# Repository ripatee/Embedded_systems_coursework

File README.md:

# Embedded_systems_coursework
Course work for Embedded systems project -course. Project is nRF9160 based temperature sensor with an eINK display.

## Features
- Based on nRF9160 SIP
- Measures (at least) temperature and humidity
- Shows measurements at eINK screen
- Sends measurements over M-LTE or NB-IOT
- Additionally sends current GPS coordinates
- Battery powered

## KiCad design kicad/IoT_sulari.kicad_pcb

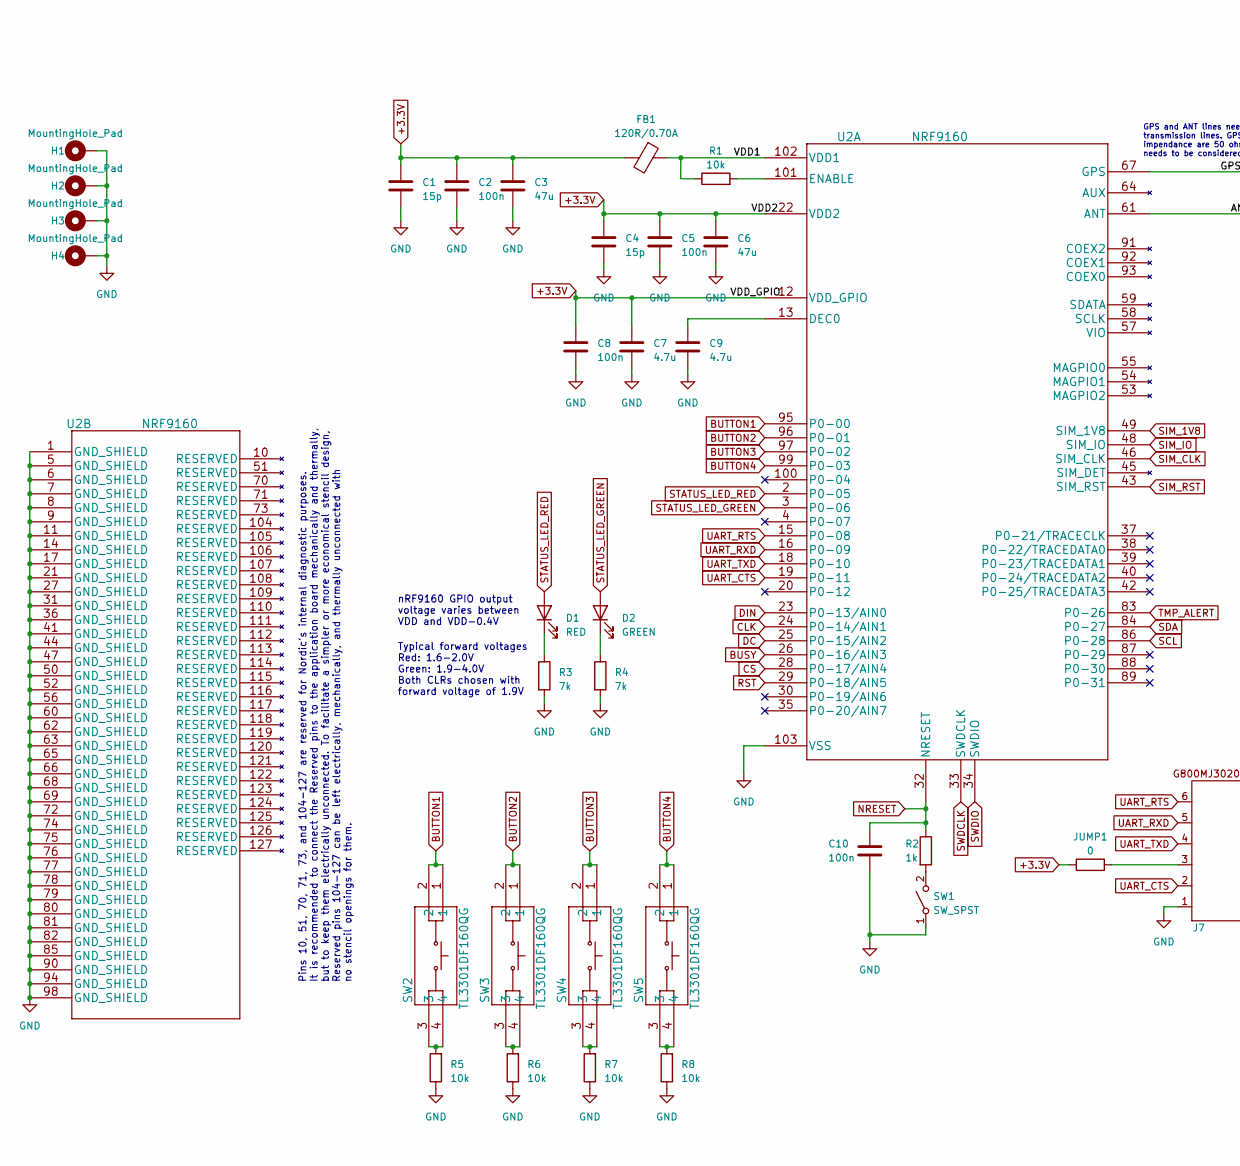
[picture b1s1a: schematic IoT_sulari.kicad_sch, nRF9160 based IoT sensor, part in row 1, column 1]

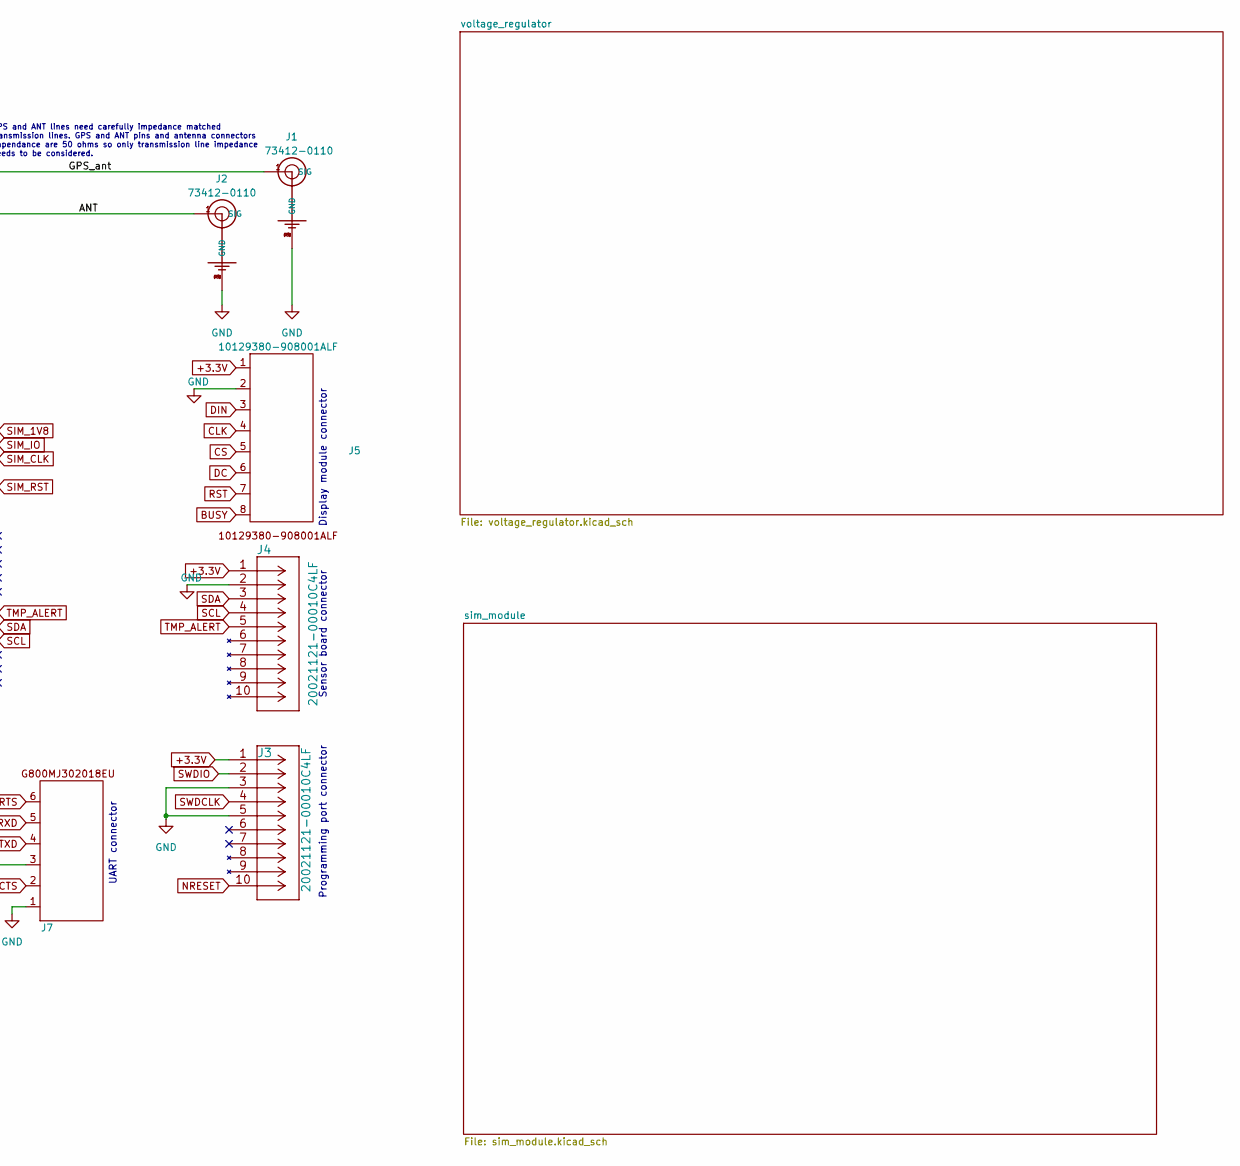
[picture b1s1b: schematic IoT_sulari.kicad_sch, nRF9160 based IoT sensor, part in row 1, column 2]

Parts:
C1, C4: 15p; C_0603_1608Metric_Pad1.08x0.95mm_HandSolder; Digikey 1292-1487-1-ND
C2, C5, C8, C10: 100n; C_0603_1608Metric_Pad1.08x0.95mm_HandSolder; Digikey 587-1245-1-ND
C3, C6: 47u; C_0603_1608Metric_Pad1.08x0.95mm_HandSolder; Digikey 490-GRM188R60G476ME01DCT-ND
C7, C9: 4.7u; C_0603_1608Metric_Pad1.08x0.95mm_HandSolder; Digikey 1276-1045-1-ND
D1: RED; LED_0603_1608Metric_Pad1.05x0.95mm_HandSolder; Digikey 1080-1400-1-ND
D2: GREEN; LED_0603_1608Metric_Pad1.05x0.95mm_HandSolder; Digikey 492-2523-1-ND
FB1: 120R/0.70A; R_0402_1005Metric_Pad0.72x0.64mm_HandSolder; Digikey 445-MMZ1005S121HTD25CT-ND
H1, H2, H3, H4: MountingHole_Pad; MountingHole_3.2mm_M3_Pad_Via
J1, J2: 73412-0110; MOLEX_73412-0110; Digikey WM5587CT-ND
J3, J4: 20021121-00010C4LF; Digikey 609-3695-1-ND
J5: 10129380-908001ALF; Digikey 10129380-908001ALF-ND
J7: G800MJ302018EU; Digikey 664-G800MJ302018EUCT-ND
JUMP1: 0; R_0805_2012Metric_Pad1.20x1.40mm_HandSolder
R1, R5, R6, R7, R8: 10k; R_0603_1608Metric_Pad0.98x0.95mm_HandSolder; Digikey RNCP0603FTD10K0CT-ND
R2: 1k; R_0603_1608Metric_Pad0.98x0.95mm_HandSolder; Digikey RNCP0603FTD1K00CT-ND
R3, R4: 7k; R_0603_1608Metric_Pad0.98x0.95mm_HandSolder; Digikey 311-6.98KHRCT-ND
SW1: SW_SPST; TL3302BF180QG; Digikey EG2529CT-ND
SW2, SW3, SW4, SW5: TL3301DF160QG
U2: NRF9160; NRF9160-SICA-B1A-R; Digikey 4823-NRF9160-SICA-B1A-RCT-ND

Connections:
+3.3V: C1.1, C2.1, C3.1, C4.1, C5.1, C6.1, C7.1, C8.1, FB1.2, J3.1, J4.1, J5.1, JUMP1.1, U2.12 (VDD_GPIO), U2.22 (VDD2); also elsewhere on the board
/ANT: J2.1 (SIG), U2.61 (ANT)
/GPS_ant: J1.1 (SIG), U2.67 (GPS)
/VDD1: FB1.1, R1.1, U2.102 (VDD1)
BUSY: J5.8, U2.26 (P0-16/AIN3)
BUTTON1: SW2.1, SW2.2, U2.95 (P0-00)
BUTTON2: SW3.1, SW3.2, U2.96 (P0-01)
BUTTON3: SW4.1, SW4.2, U2.97 (P0-02)
BUTTON4: SW5.1, SW5.2, U2.99 (P0-03)
CLK: J5.4, U2.24 (P0-14/AIN1)
CS: J5.5, U2.28 (P0-17/AIN4)
DC: J5.6, U2.25 (P0-15/AIN2)
DIN: J5.3, U2.23 (P0-13/AIN0)
GND: C1.2, C2.2, C3.2, C4.2, C5.2, C6.2, C7.2, C8.2, C9.2, C10.2, H1.1, H2.1, H3.1, H4.1, J1.2 (GND), J1.3 (GND), J1.4 (GND), J2.2 (GND), J2.3 (GND), J2.4 (GND), J3.3, J3.5, J4.2, J5.2, J7.1, R3.2, R4.2, R5.1, R6.1, R7.1, R8.1, SW1.1 (A), U2.1 (GND_SHIELD), U2.5 (GND_SHIELD), U2.6 (GND_SHIELD), U2.7 (GND_SHIELD), U2.8 (GND_SHIELD), U2.9 (GND_SHIELD), U2.11 (GND_SHIELD), U2.14 (GND_SHIELD), U2.17 (GND_SHIELD), U2.21 (GND_SHIELD), U2.27 (GND_SHIELD), U2.31 (GND_SHIELD), U2.36 (GND_SHIELD), U2.41 (GND_SHIELD), U2.44 (GND_SHIELD), U2.47 (GND_SHIELD), U2.50 (GND_SHIELD), U2.52 (GND_SHIELD), U2.56 (GND_SHIELD), U2.60 (GND_SHIELD), U2.62 (GND_SHIELD), U2.63 (GND_SHIELD), U2.65 (GND_SHIELD), U2.66 (GND_SHIELD), U2.68 (GND_SHIELD), U2.69 (GND_SHIELD), U2.72 (GND_SHIELD), U2.74 (GND_SHIELD), U2.75 (GND_SHIELD), U2.76 (GND_SHIELD), U2.77 (GND_SHIELD), U2.78 (GND_SHIELD), U2.79 (GND_SHIELD), U2.80 (GND_SHIELD), U2.81 (GND_SHIELD), U2.82 (GND_SHIELD), U2.85 (GND_SHIELD), U2.90 (GND_SHIELD), U2.94 (GND_SHIELD), U2.98 (GND_SHIELD), U2.103 (VSS); also elsewhere on the board
NRESET: C10.1, J3.10, R2.1, U2.32 (NRESET)
unnamed: D1.1 (K), R3.1
unnamed: D2.1 (K), R4.1
unnamed 17: J7.3, JUMP1.2; also elsewhere on the board
unnamed: R5.2, SW2.3, SW2.4
unnamed: R6.2, SW3.3, SW3.4
unnamed: R7.2, SW4.3, SW4.4
unnamed: R8.2, SW5.3, SW5.4
unnamed: R2.2, SW1.2 (B)
unnamed: C9.1, U2.13 (DEC0)
unnamed: R1.2, U2.101 (ENABLE)
RST: J5.7, U2.29 (P0-18/AIN5)
SCL: J4.4, U2.86 (P0-28)
SDA: J4.3, U2.84 (P0-27)
SIM_1V8: U2.49 (SIM_1V8); also elsewhere on the board
SIM_CLK: U2.46 (SIM_CLK); also elsewhere on the board
SIM_IO: U2.48 (SIM_IO); also elsewhere on the board
SIM_RST: U2.43 (SIM_RST); also elsewhere on the board
STATUS_LED_GREEN: D2.2 (A), U2.3 (P0-06)
STATUS_LED_RED: D1.2 (A), U2.2 (P0-05)
SWDCLK: J3.4, U2.33 (SWDCLK)
SWDIO: J3.2, U2.34 (SWDIO)
TMP_ALERT: J4.5, U2.83 (P0-26)
UART_CTS: J7.2, U2.19 (P0-11)
UART_RTS: J7.6, U2.15 (P0-08)
UART_RXD: J7.5, U2.16 (P0-09)
UART_TXD: J7.4, U2.18 (P0-10)

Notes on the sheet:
Sensor board connector
Display module connector
Programming port connector
Pins 10, 51, 70, 71, 73, and 104-127 are reserved for Nordic's internal diagnostic purposes. It is recommended to connect the Reserved pins to the application board mechanically and thermally, but to keep them electrically unconnected. To facilitate a simpler or more economical stencil design, Rese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
nRF9160 GPIO output voltage varies between VDD and VDD-0.4V
UART connector
GPS and ANT lines need carefully impedance matched transmission lines. GPS and ANT pins and antenna connectors impendance are 50 ohms so only transmission line impedance needs to be considered.
Typical forward voltages Red: 1.6-2.0V Green: 1.9-4.0V Both CLRs chosen with forward voltage of 1.9V

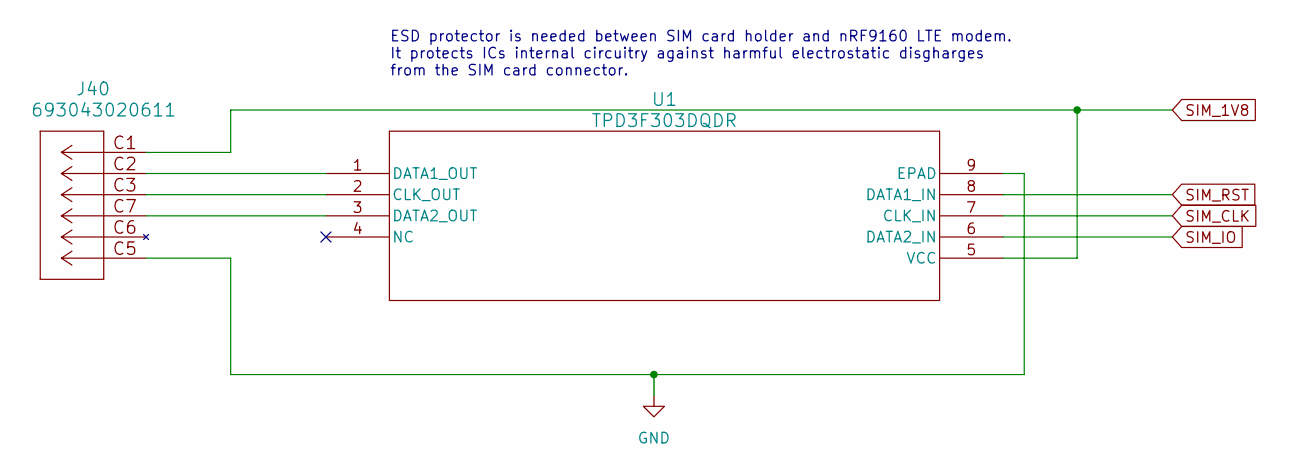
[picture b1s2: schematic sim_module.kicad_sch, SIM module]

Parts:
J40: 693043020611; Digikey 296-28299-1-ND
U1: TPD3F303DQDR

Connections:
GND: J40.C5, U1.9 (EPAD); also elsewhere on the board
unnamed 27: J40.C3, U1.2 (CLK_OUT); also elsewhere on the board
unnamed 28: J40.C2, U1.1 (DATA1_OUT); also elsewhere on the board
unnamed 29: J40.C7, U1.3 (DATA2_OUT); also elsewhere on the board
SIM_1V8: J40.C1, U1.5 (VCC); also elsewhere on the board

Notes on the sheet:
ESD protector is needed between SIM card holder and nRF9160 LTE modem. It protects ICs internal circuitry against harmful electrostatic disgharges from the SIM card connector.

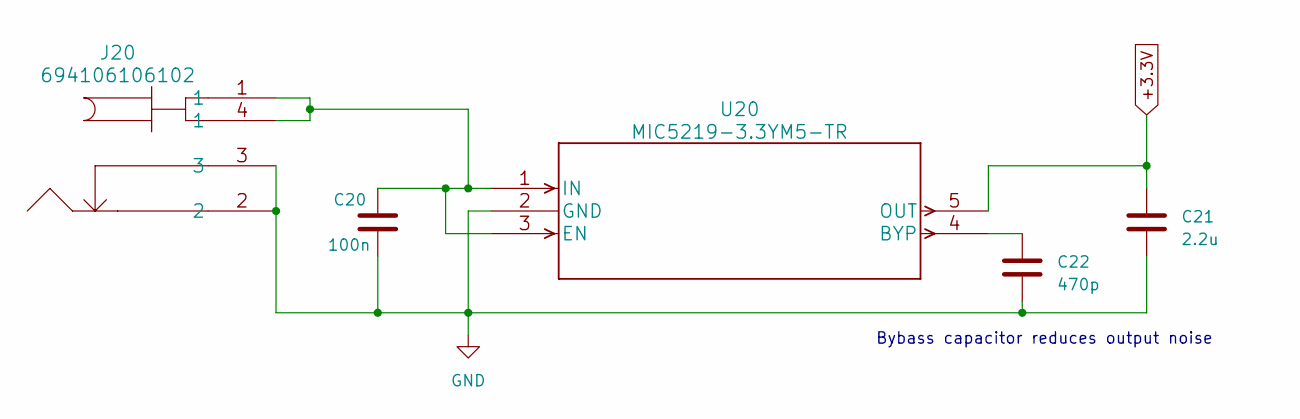
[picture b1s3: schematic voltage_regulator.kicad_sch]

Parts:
C20: 100n; C_0603_1608Metric_Pad1.08x0.95mm_HandSolder; Digikey 587-1245-1-ND
C21: 2.2u; C_0603_1608Metric_Pad1.08x0.95mm_HandSolder; Digikey 587-1430-1-ND
C22: 470p; C_0603_1608Metric_Pad1.08x0.95mm_HandSolder; Digikey 1292-1530-1-ND
J20: 694106106102; Digikey 732-5929-1-ND
U20: MIC5219-3.3YM5-TR; Digikey 576-1281-1-ND

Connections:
+3.3V: C21.1, U20.5 (OUT); also elsewhere on the board
GND: C20.2, C21.2, C22.2, J20.2, J20.3, U20.2 (GND); also elsewhere on the board
unnamed: C22.1, U20.4 (BYP)
unnamed: C20.1, J20.1, J20.4 (1), U20.1 (IN), U20.3 (EN)

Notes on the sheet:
Bybass capacitor reduces output noise

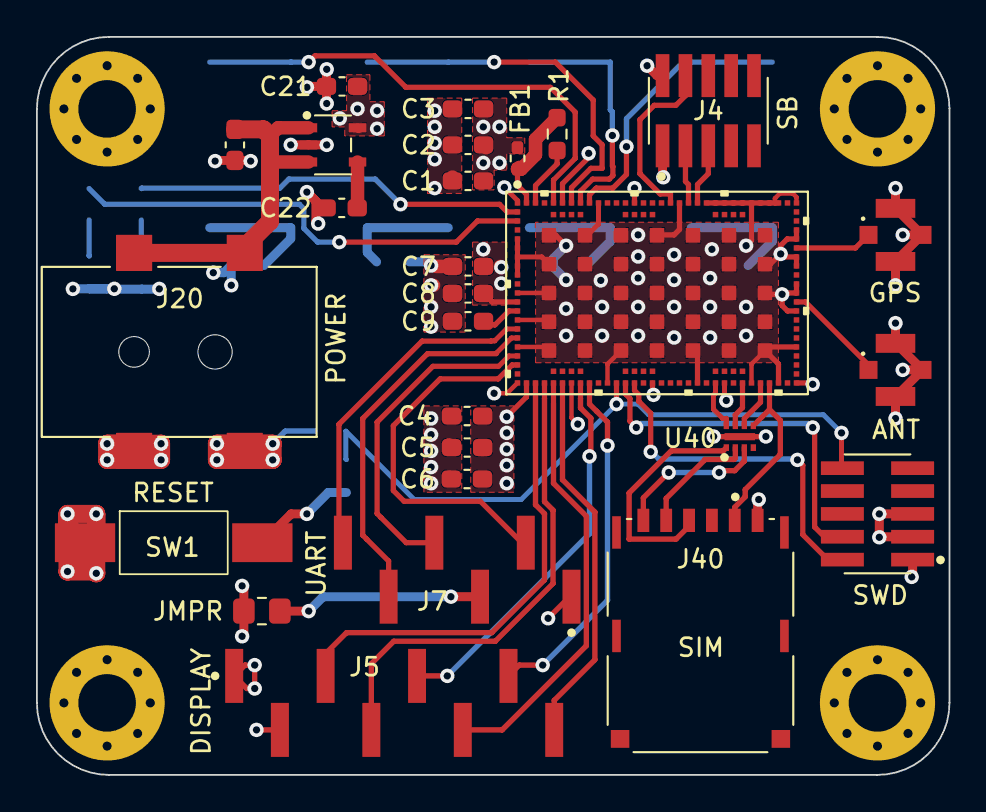
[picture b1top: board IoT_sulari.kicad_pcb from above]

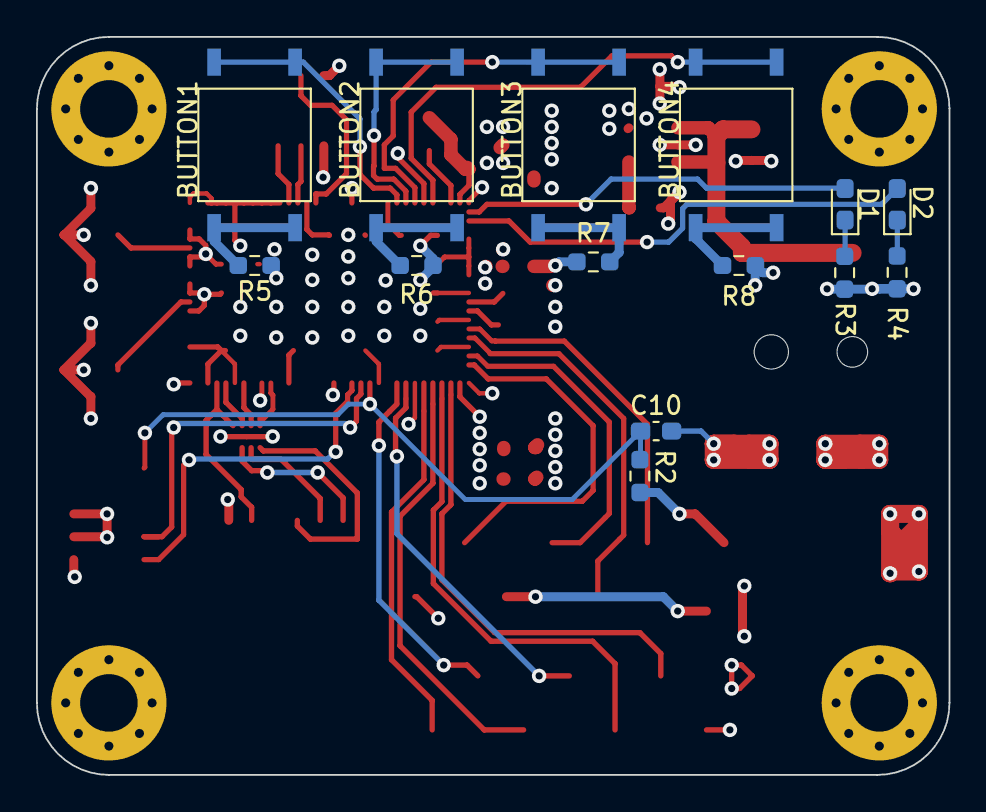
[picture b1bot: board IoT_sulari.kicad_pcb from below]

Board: 4 copper layers, 50.7 x 41.0 mm, 45 parts (14 on the bottom side), 46 nets.

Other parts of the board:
JMPR: 0; R_0805_2012Metric_Pad1.20x1.40mm_HandSolder
U40: TPD3F303DPVR

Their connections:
+3.3V: JMPR.1; also elsewhere on the board
GND: U40.9 (EPAD); also elsewhere on the board
unnamed 17: JMPR.2; also elsewhere on the board
unnamed 27: U40.2 (CLK_OUT); also elsewhere on the board
unnamed 28: U40.1 (DATA1_OUT); also elsewhere on the board
unnamed 29: U40.3 (DATA2_OUT); also elsewhere on the board
SIM_1V8: U40.5 (VCC); also elsewhere on the board
SIM_CLK: U40.7 (CLK_IN); also elsewhere on the board
SIM_IO: U40.6 (DATA2_IN); also elsewhere on the board
SIM_RST: U40.8 (DATA1_IN); also elsewhere on the board

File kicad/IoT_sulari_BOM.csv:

"Reference","Value","Footprint","Datasheet","Digikey","MANUFACTURER","Qty"
"C1, C4","15p","Capacitor_SMD:C_0603_1608Metric_Pad1.08x0.95mm_HandSolder","~","1292-1487-1-ND","","2"
"C2, C5, C7, C10, C20","100n","Capacitor_SMD:C_0603_1608Metric_Pad1.08x0.95mm_HandSolder","~","587-1245-1-ND","","5"
"C3, C6","47u","Capacitor_SMD:C_0603_1608Metric_Pad1.08x0.95mm_HandSolder","~","490-GRM188R60G476ME01DCT-ND","","2"
"C8, C9","4.7u","Capacitor_SMD:C_0603_1608Metric_Pad1.08x0.95mm_HandSolder","~","1276-1045-1-ND","","2"
"C21","2.2u","Capacitor_SMD:C_0603_1608Metric_Pad1.08x0.95mm_HandSolder","~","587-1430-1-ND","","1"
"C22","470p","Capacitor_SMD:C_0603_1608Metric_Pad1.08x0.95mm_HandSolder","~","1292-1530-1-ND","","1"
"D1","RED","LED_SMD:LED_0603_1608Metric_Pad1.05x0.95mm_HandSolder","~","1080-1400-1-ND","","1"
"D2","GREEN","LED_SMD:LED_0603_1608Metric_Pad1.05x0.95mm_HandSolder","~","492-2523-1-ND","","1"
"FB1","120R/0.70A","Resistor_SMD:R_0402_1005Metric_Pad0.72x0.64mm_HandSolder","~","445-MMZ1005S121HTD25CT-ND","","1"
"H1-H4","MountingHole_Pad","MountingHole:MountingHole_3.2mm_M3_Pad_Via","~","","","4"
"J1, J2","73412-0110","73412-0110:MOLEX_73412-0110","","WM5587CT-ND","Molex","2"
"J3, J4, J6","20021121-00010C4LF","20021121-00010C4LF:20021121-00010C4LF","","609-3695-1-ND","","3"
"J7","","G800MJ302018EU:G800MJ302018EU","","664-G800MJ302018EUCT-ND","","1"
"J20","694106106102","694106106102:694106106102","","732-5929-1-ND","","1"
"J40","693043020611","693043020611:693043020611","","296-28299-1-ND","","1"
"R1, R5-R8","10k","Resistor_SMD:R_0603_1608Metric_Pad0.98x0.95mm_HandSolder","~","RNCP0603FTD10K0CT-ND","","5"
"R2","1k","Resistor_SMD:R_0603_1608Metric_Pad0.98x0.95mm_HandSolder","~","RNCP0603FTD1K00CT-ND","","1"
"R3, R4","7k","Resistor_SMD:R_0603_1608Metric_Pad0.98x0.95mm_HandSolder","~","311-6.98KHRCT-ND","","2"
"SW1","SW_SPST","TL3302BF180QG:TL3302BF180QG","","EG2529CT-ND","","1"
"SW2-SW5","TL3301DF160QG","TL3301DF160QG:TL3301DF160QG","","","","4"
"U2","NRF9160","NRF-9160-SICA-B1A-R:NRF9160-SICA-B1A-R","","4823-NRF9160-SICA-B1A-RCT-ND","","1"
"U20","MIC5219-3.3YM5-TR","MIC5219-3.3YM5-TR:MIC5219-3.3YM5-TR","","576-1281-1-ND","","1"
"U40","TPD3F303DPVR","TPD3F303DPVR:TPD3F303DPVR","","732-5954-1-ND","","1"

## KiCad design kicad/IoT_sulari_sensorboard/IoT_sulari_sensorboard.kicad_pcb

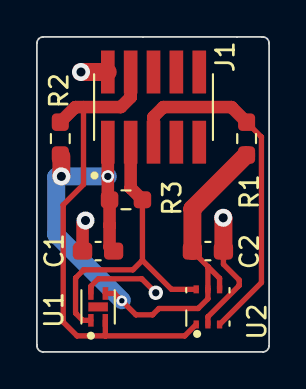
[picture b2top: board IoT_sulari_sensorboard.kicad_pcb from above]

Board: 2 copper layers, 12.9 x 17.5 mm, 8 parts (0 on the bottom side), 5 nets.

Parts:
C1, C2: 100n; C_0603_1608Metric_Pad1.08x0.95mm_HandSolder
J1: 20021121-00010C4LF
R1, R2, R3: 5k; R_0603_1608Metric_Pad0.98x0.95mm_HandSolder
U1: SHT40-AD1B-R3; SHT40-AD1B-R2
U2: TMP117MAIDRVT

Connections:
/GND: C1.2, C2.2, J1.2, U1.4 (VSS), U2.2 (GND)
/SCL: J1.4, R2.2, U1.2 (SCL), U2.1 (SCL)
/SDA: J1.3, R3.2, U1.1 (SDA), U2.6 (SDA)
/TMP_ALERT: J1.5, R1.2, U2.3 (ALERT)
/VCC: C1.1, C2.1, J1.1, R1.1, R2.1, R3.1, U1.3 (VDD), U2.4 (ADD0), U2.5 (V+)

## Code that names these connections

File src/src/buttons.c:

#include <zephyr/device.h>
#include <zephyr/devicetree.h>
#include <zephyr/drivers/gpio.h>
#include <zephyr/logging/log.h>

#include "buttons.h"
#include "sms_wrapper.h"
#include "sensors.h"

#define SW0_NODE    DT_ALIAS(sw0)
#define SW1_NODE    DT_ALIAS(sw1)
#define SW2_NODE    DT_ALIAS(sw2)
#define SW3_NODE    DT_ALIAS(sw3)

LOG_MODULE_REGISTER(BUTTONS, LOG_LEVEL_DBG);

static const struct gpio_dt_spec button0 = GPIO_DT_SPEC_GET(SW0_NODE, gpios);
static const struct gpio_dt_spec button1 = GPIO_DT_SPEC_GET(SW1_NODE, gpios);
static const struct gpio_dt_spec button2 = GPIO_DT_SPEC_GET(SW2_NODE, gpios);
static const struct gpio_dt_spec button3 = GPIO_DT_SPEC_GET(SW3_NODE, gpios);

static struct gpio_callback button0_cb_data;
static struct gpio_callback button1_cb_data;
static struct gpio_callback button2_cb_data;
static struct gpio_callback button3_cb_data;

static void button0_cb(const struct device *dev, struct gpio_callback *cb, uint32_t pins)
{
    LOG_INF("Button 0 pressed.");
}

static void button1_cb(const struct device *dev, struct gpio_callback *cb, uint32_t pins)
{
    LOG_INF("Button 1 pressed.");
}

static void button2_cb(const struct device *dev, struct gpio_callback *cb, uint32_t pins)
{
    LOG_INF("Button 2 pressed.");
}

static void button3_cb(const struct device *dev, struct gpio_callback *cb, uint32_t pins)
{
    LOG_INF("Button 3 pressed.");
}

void buttons_init(void)
{
    int ret;

    if (!device_is_ready(button0.port)) {
        return;
    }

    if (!device_is_ready(button1.port)) {
        return;
    }

    if (!device_is_ready(button2.port)) {
        return;
    }

    if (!device_is_ready(button3.port)) {
        return;
    }

    ret = gpio_pin_configure_dt(&button0, GPIO_INPUT);
	if (ret < 0) {
		return;
	}

    ret = gpio_pin_configure_dt(&button1, GPIO_INPUT);
	if (ret < 0) {
		return;
	}

    ret = gpio_pin_configure_dt(&button2, GPIO_INPUT);
	if (ret < 0) {
		return;
	}

    ret = gpio_pin_configure_dt(&button3, GPIO_INPUT);
	if (ret < 0) {
		return;
	}

    ret = gpio_pin_interrupt_configure_dt(&button0, GPIO_INT_EDGE_TO_ACTIVE );
    ret = gpio_pin_interrupt_configure_dt(&button1, GPIO_INT_EDGE_TO_ACTIVE );
    ret = gpio_pin_interrupt_configure_dt(&button2, GPIO_INT_EDGE_TO_ACTIVE );
    ret = gpio_pin_interrupt_configure_dt(&button3, GPIO_INT_EDGE_TO_ACTIVE );

    gpio_init_callback(&button0_cb_data, button0_cb, BIT(button0.pin)); 	
    gpio_init_callback(&button1_cb_data, button1_cb, BIT(button1.pin)); 	
    gpio_init_callback(&button2_cb_data, button2_cb, BIT(button2.pin)); 	
    gpio_init_callback(&button3_cb_data, button3_cb, BIT(button3.pin)); 	

    gpio_add_callback(button0.port, &button0_cb_data);
    gpio_add_callback(button1.port, &button1_cb_data);
    gpio_add_callback(button2.port, &button2_cb_data);
    gpio_add_callback(button3.port, &button3_cb_data);
}

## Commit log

2023-01-25 Add placeholder files
2023-03-02 Initialize KiCad project
2023-03-02 Testing kicad
2023-03-02 Add .gitignore, remove backups folder
2023-03-02 Add project specifiaciton in LaTeX format
2023-03-02 Added test file
2023-03-02 deleted test file
2023-03-08 testi
2023-03-14 Add nRF9160 to KiCad project
2023-03-16 added TCR2EF33 symbol to kicad
2023-03-16 Added NRF9160 symbol and footprint
2023-03-16 Added TMP117, HDC2010, TPD3F3 and TCR2EF33 symbols to KiCad and component documents to doc.
2023-03-17 Added hierarchical sheets to different components
2023-03-21 Updated nrf9160 symbols for easier use, added sim card holder and doc, added first connections to mcu
2023-03-22 Kosteussensori ja regulaattori footprintit
2023-03-22 added power jack and usb connector
2023-03-23 Updated USB module
2023-03-24 sensorboard modification, regulator modification, datasheets
2023-03-24 ESD component fo USB
2023-03-24 voltage regulator update
2023-03-24 added status leds
2023-03-24 sensorboard schema + esd datasheet
2023-03-24 added comments and muokkasin komponenttiennumeroinnin selvemmäksi.
2023-03-24 nreset
2023-03-24 added antenna connector
2023-03-28 Added Digikey part number and footprint to symbols, added signal TMP_ALERT
2023-03-28 Added buttons and connectors
2023-03-30 6-pin connector footprint and symbol
2023-03-30 schematic editing, led selection
2023-03-30 footprint 9-pin
2023-03-30 kommitti
2023-04-06 USB-module delete
2023-04-06 added footprints and Digikey codes
2023-04-06 reset button footprint
2023-04-06 PCB update
2023-04-06 Reset button footprint added to pcb
2023-04-11 Updated PCB design rules and layout to correct placing around nRF9160
2023-04-12 viesti
2023-04-12 updated PCB
2023-04-14 kytkimen siirto
2023-04-14 TL3302 footprint edit
2023-04-14 moro
2023-04-14 sensorboard project add
2023-04-14 added board outline and inner copper layers, layout finalization
2023-04-14 sensorboard pcb drawing
2023-04-14 routing
2023-04-19 Finished routing and added vias
2023-04-21 csv document
2023-04-21 csv delete
2023-04-25 sensorboard edit
2023-05-05 Fixed drc errors for PCB
2023-05-05 sensorboard modify and mainboard connector add
2023-05-05 sensorboard DRC fix
2023-05-05 changed Display connector
2023-05-05 Edited copper fill zones, final touches
2023-05-05 ESD change
2023-05-09 Add sensorboard manufacturing files
2023-05-09 Revert "ESD change"
    This reverts commit acabe66db7bce87ed7ccd6d28b87d0a8866a87e9.
2023-05-09 Regenerate main board manufacturing files
2023-09-23 Initial commit for bring-up
2023-09-29 Test codes to test different peripherals
2023-09-30 Add minimal sensor functionality (logs values to console)
2023-09-30 Add buttons skeleton
2023-09-30 Add LTE skeleton
2023-10-02 PoC MQTT functionality
2023-10-02 Correct indentation
2023-10-02 Add SMS functionality
2023-10-02 Change CONFIG_SMS_RECEIVER_NUMBER to empty string
2023-10-02 Remove not needed header includes
2023-10-08 Start EPD develop
2023-10-11 Intermediate commit with SSD16XX driver
2023-10-27 Intermediate commit to sync files
2023-10-31 Sync commit
2023-10-31 Remove all but display code
2023-11-03 Change display to OLED
2023-11-10 Update OLED functionality
2023-11-10 Fix colors
2023-11-11 Remove epd driver skeleton
2023-11-11 Add OLED display (main-loop update not working yet)
2023-11-11 Split main function to threads
2024-06-27 Update to smaller eink
2024-09-14 Lots of fixes and stuff

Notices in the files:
parts and their libraries:
Copyright 2021 Accelerated Designs. All rights reserved.
